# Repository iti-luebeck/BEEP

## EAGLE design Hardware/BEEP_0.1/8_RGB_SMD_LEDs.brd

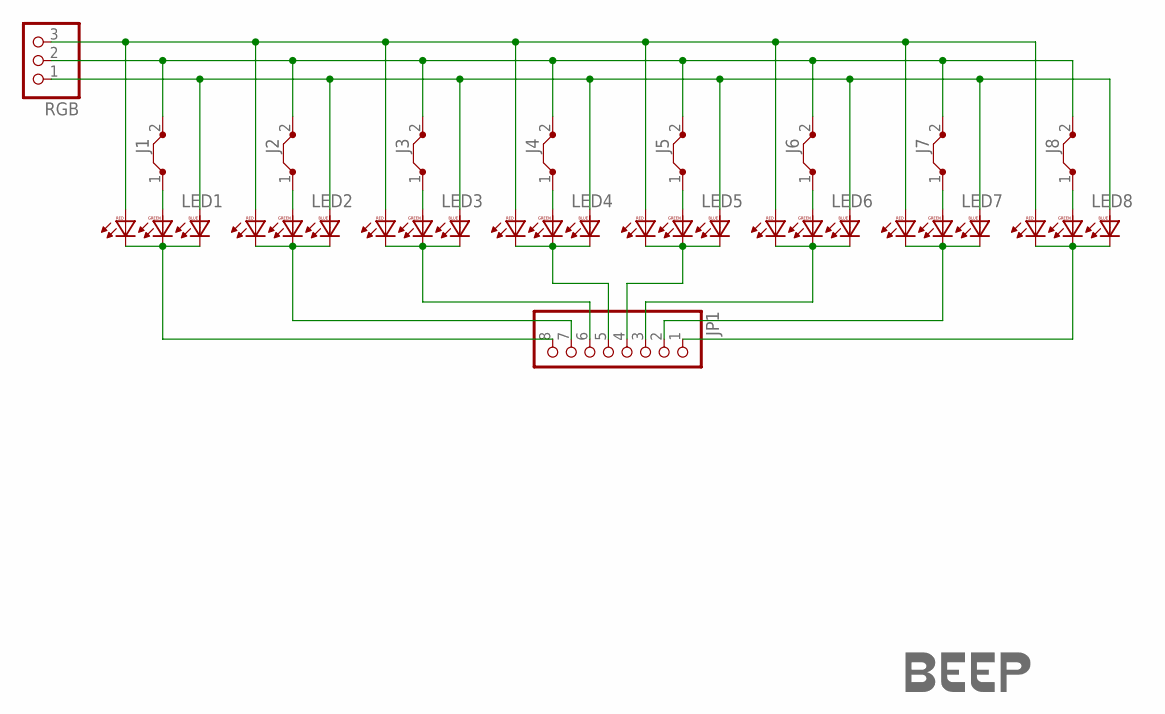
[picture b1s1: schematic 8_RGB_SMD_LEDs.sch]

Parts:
J1, J2, J3, J4, J5, J6, J7, J8: J7MM; 07
JP1: PINHD-1X8; 1X08
LED1, LED2, LED3, LED4, LED5, LED6, LED7, LED8: F503605050; 5050LED
RGB: PINHD-1X3; 1X03
U$5: LOGO-COPPER7; COPPER7

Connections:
unnamed: J1.2, J2.2, J3.2, J4.2, J5.2, J6.2, J7.2, J8.2, RGB.2
unnamed: J1.1, LED1.G1 (GA)
unnamed: JP1.8, LED1.B2 (BC), LED1.G2 (GC), LED1.R2 (RC)
unnamed: JP1.7, LED2.B2 (BC), LED2.G2 (GC), LED2.R2 (RC)
unnamed: JP1.6, LED3.B2 (BC), LED3.G2 (GC), LED3.R2 (RC)
unnamed: JP1.5, LED4.B2 (BC), LED4.G2 (GC), LED4.R2 (RC)
unnamed: J2.1, LED2.G1 (GA)
unnamed: JP1.4, LED5.B2 (BC), LED5.G2 (GC), LED5.R2 (RC)
unnamed: JP1.3, LED6.B2 (BC), LED6.G2 (GC), LED6.R2 (RC)
unnamed: JP1.2, LED7.B2 (BC), LED7.G2 (GC), LED7.R2 (RC)
unnamed: JP1.1, LED8.B2 (BC), LED8.G2 (GC), LED8.R2 (RC)
unnamed: J3.1, LED3.G1 (GA)
unnamed: J4.1, LED4.G1 (GA)
unnamed: J5.1, LED5.G1 (GA)
unnamed: J6.1, LED6.G1 (GA)
unnamed: J7.1, LED7.G1 (GA)
unnamed: LED1.R1 (RA), LED2.R1 (RA), LED3.R1 (RA), LED4.R1 (RA), LED5.R1 (RA), LED6.R1 (RA), LED7.R1 (RA), LED8.R1 (RA), RGB.3
unnamed: J8.1, LED8.G1 (GA)
unnamed: LED1.B1 (BA), LED2.B1 (BA), LED3.B1 (BA), LED4.B1 (BA), LED5.B1 (BA), LED6.B1 (BA), LED7.B1 (BA), LED8.B1 (BA), RGB.1

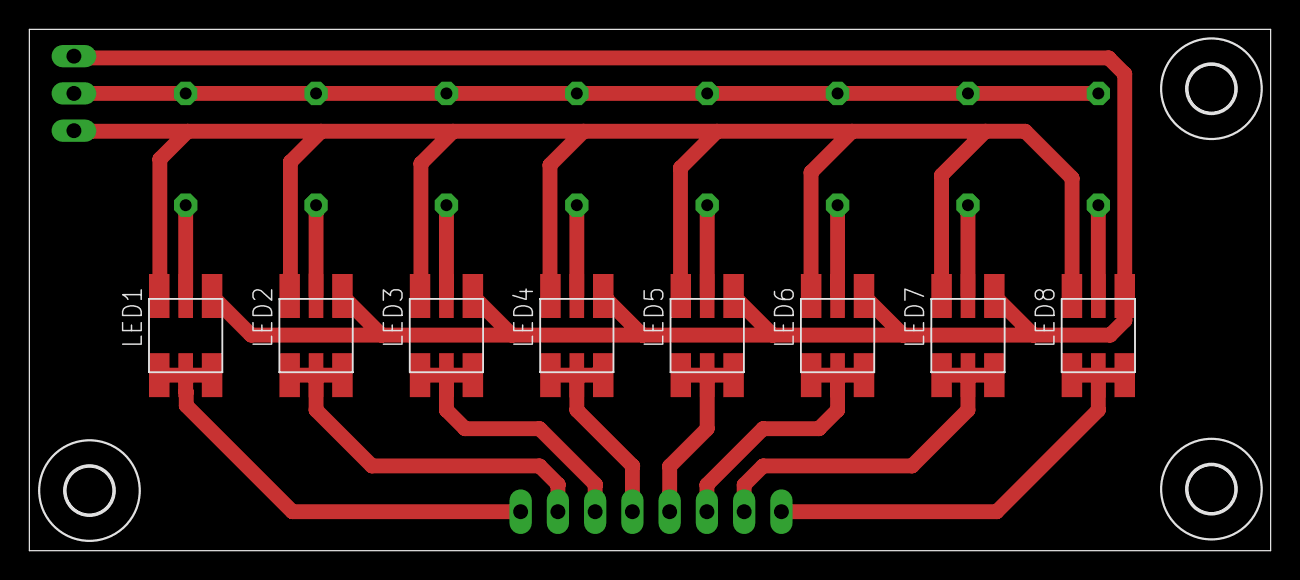
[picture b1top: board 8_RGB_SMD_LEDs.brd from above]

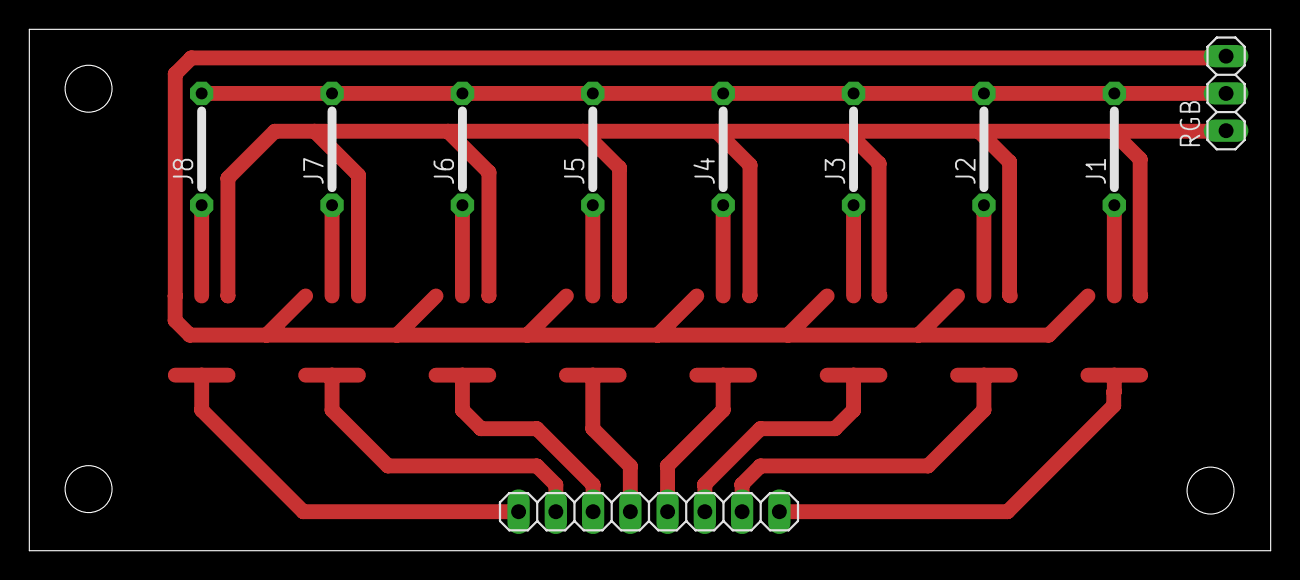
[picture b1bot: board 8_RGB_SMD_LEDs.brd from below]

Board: 2 copper layers, 84.6 x 35.5 mm, 22 parts (10 on the bottom side), 19 nets.

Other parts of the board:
U$1, U$2, U$3: 3,2

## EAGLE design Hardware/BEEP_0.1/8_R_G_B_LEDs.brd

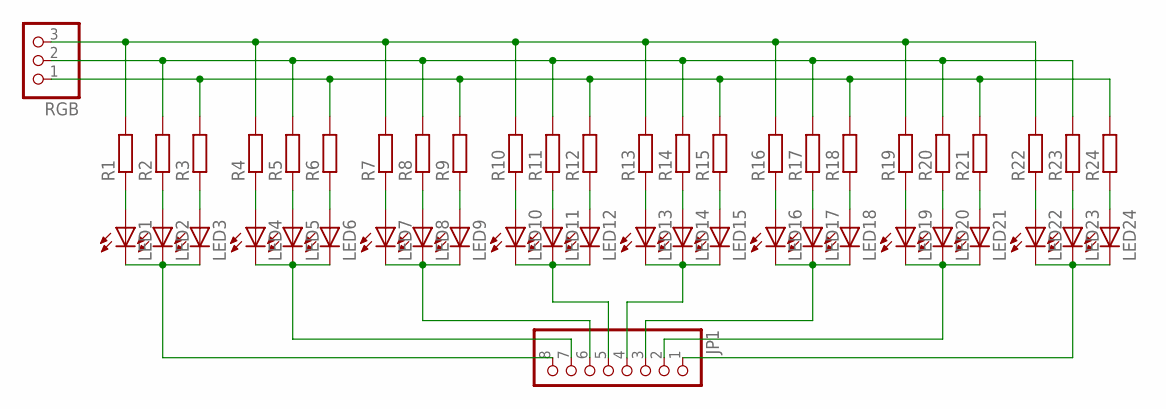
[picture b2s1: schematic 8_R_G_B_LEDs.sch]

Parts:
JP1: PINHD-1X8; 1X08
LED1, LED2, LED3, LED4, LED5, LED6, LED7, LED8, LED9, LED10, LED11, LED12, LED13, LED14, LED15, LED16, LED17, LED18, LED19, LED20, LED21, LED22, LED23, LED24: LED5MM
R1, R2, R3, R4, R5, R6, R7, R8, R9, R10, R11, R12, R13, R14, R15, R16, R17, R18, R19, R20, R21, R22, R23, R24: R-EU_0207/7; 0207/7
RGB: PINHD-1X3; 1X03

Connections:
unnamed: R1.2, R4.2, R7.2, R10.2, R13.2, R16.2, R19.2, R22.2, RGB.3
unnamed: R2.2, R5.2, R8.2, R11.2, R14.2, R17.2, R20.2, R23.2, RGB.2
unnamed: R3.2, R6.2, R9.2, R12.2, R15.2, R18.2, R21.2, R24.2, RGB.1
unnamed: LED1.A, R1.1
unnamed: LED2.A, R2.1
unnamed: LED3.A, R3.1
unnamed: JP1.8, LED1.K (C), LED2.K (C), LED3.K (C)
unnamed: JP1.7, LED4.K (C), LED5.K (C), LED6.K (C)
unnamed: JP1.6, LED7.K (C), LED8.K (C), LED9.K (C)
unnamed: JP1.5, LED10.K (C), LED11.K (C), LED12.K (C)
unnamed: LED4.A, R4.1
unnamed: LED5.A, R5.1
unnamed: LED6.A, R6.1
unnamed: JP1.4, LED13.K (C), LED14.K (C), LED15.K (C)
unnamed: JP1.3, LED16.K (C), LED17.K (C), LED18.K (C)
unnamed: JP1.2, LED19.K (C), LED20.K (C), LED21.K (C)
unnamed: JP1.1, LED22.K (C), LED23.K (C), LED24.K (C)
unnamed: LED7.A, R7.1
unnamed: LED8.A, R8.1
unnamed: LED9.A, R9.1
unnamed: LED10.A, R10.1
unnamed: LED11.A, R11.1
unnamed: LED12.A, R12.1
unnamed: LED13.A, R13.1
unnamed: LED14.A, R14.1
unnamed: LED15.A, R15.1
unnamed: LED16.A, R16.1
unnamed: LED17.A, R17.1
unnamed: LED18.A, R18.1
unnamed: LED19.A, R19.1
unnamed: LED20.A, R20.1
unnamed: LED21.A, R21.1
unnamed: LED22.A, R22.1
unnamed: LED23.A, R23.1
unnamed: LED24.A, R24.1

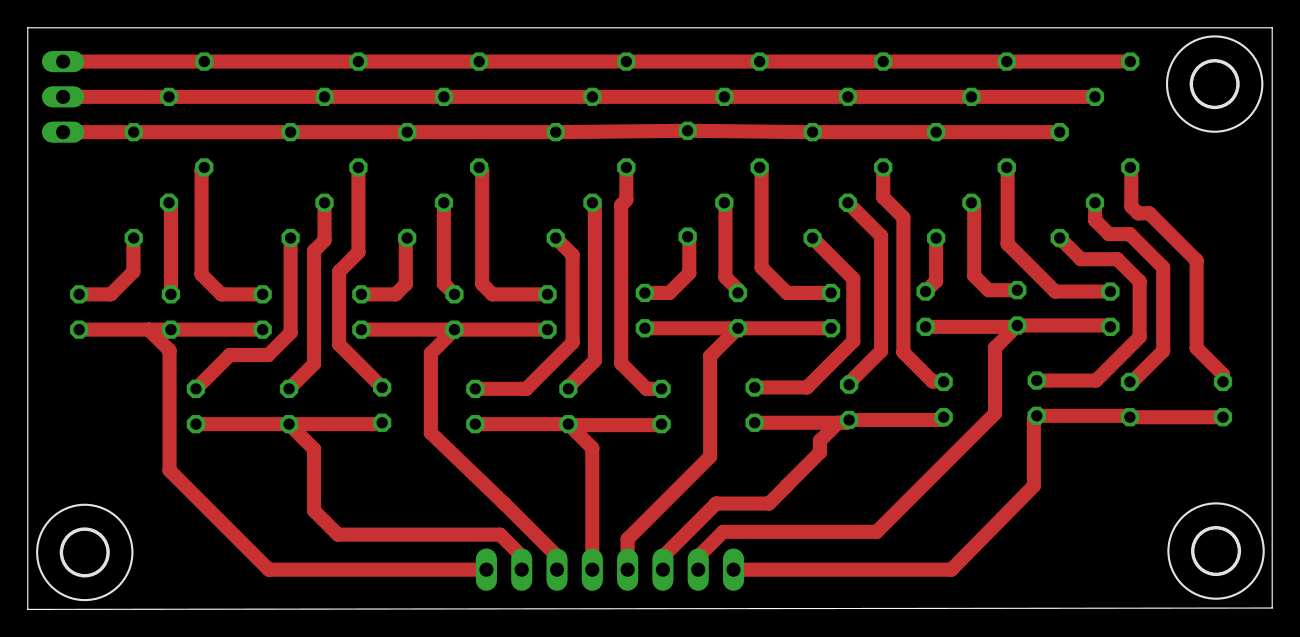
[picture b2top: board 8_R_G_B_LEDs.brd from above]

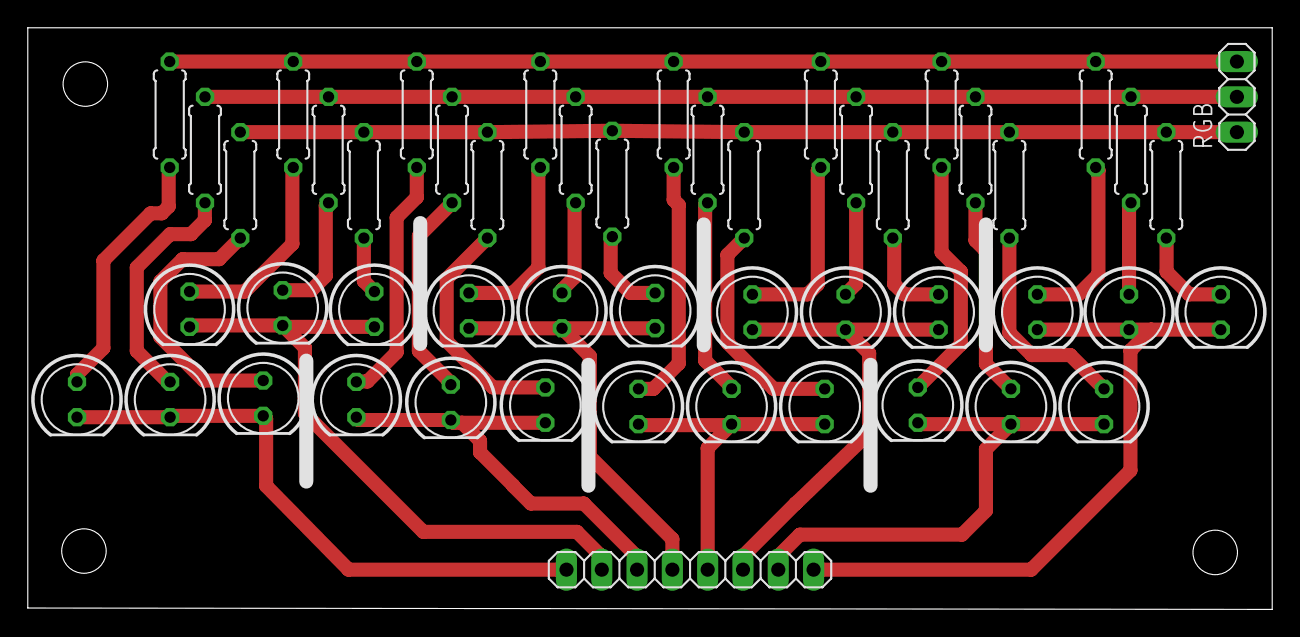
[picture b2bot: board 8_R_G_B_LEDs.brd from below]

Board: 2 copper layers, 89.5 x 41.9 mm, 53 parts (50 on the bottom side), 35 nets.

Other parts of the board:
U$1, U$2, U$3: 3,2

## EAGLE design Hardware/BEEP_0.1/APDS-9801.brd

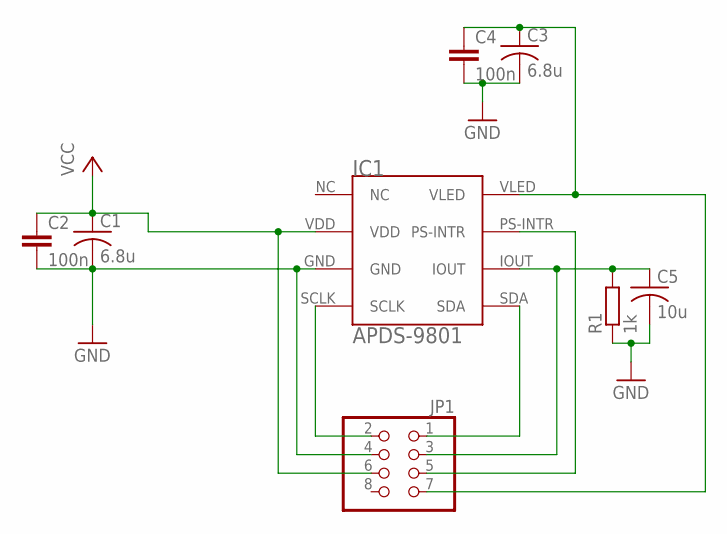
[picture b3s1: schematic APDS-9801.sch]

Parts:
C1, C3: 6.8u; C025-024X044
C2, C4: 100n; C0805
C5: 10u; C025-024X044
IC1: APDS-9801
JP1: PINHD-2X4; 2X04
R1: 1k; M0805

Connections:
GND: C1.2, C2.2, C3.2, C4.2, C5.2, IC1.GND, JP1.4, R1.1
unnamed: IC1.PS-INTR, JP1.5
unnamed: C5.1, IC1.IOUT, JP1.3, R1.2
unnamed: C3.1, C4.1, IC1.VLED, JP1.7
unnamed: IC1.SCLK, JP1.2
unnamed: IC1.SDA, JP1.1
VCC: C1.1, C2.1, IC1.VDD, JP1.6

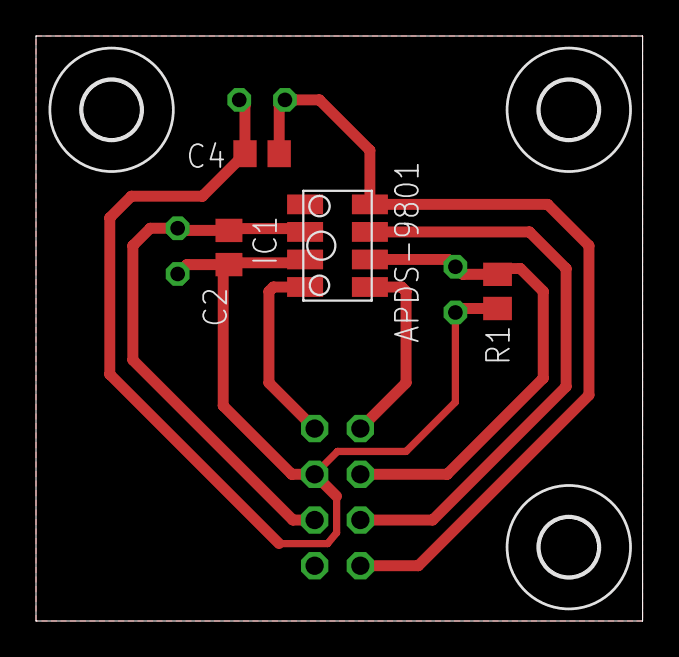
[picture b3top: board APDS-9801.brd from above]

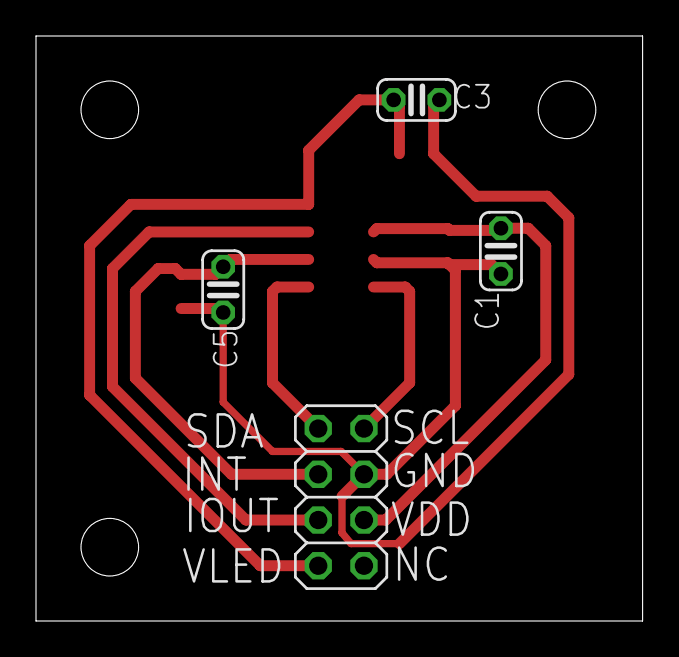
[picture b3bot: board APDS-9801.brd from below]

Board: 2 copper layers, 33.7 x 32.5 mm, 12 parts (4 on the bottom side), 7 nets.

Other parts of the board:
U$1: COPPER4
U$3, U$4, U$5: 3,2

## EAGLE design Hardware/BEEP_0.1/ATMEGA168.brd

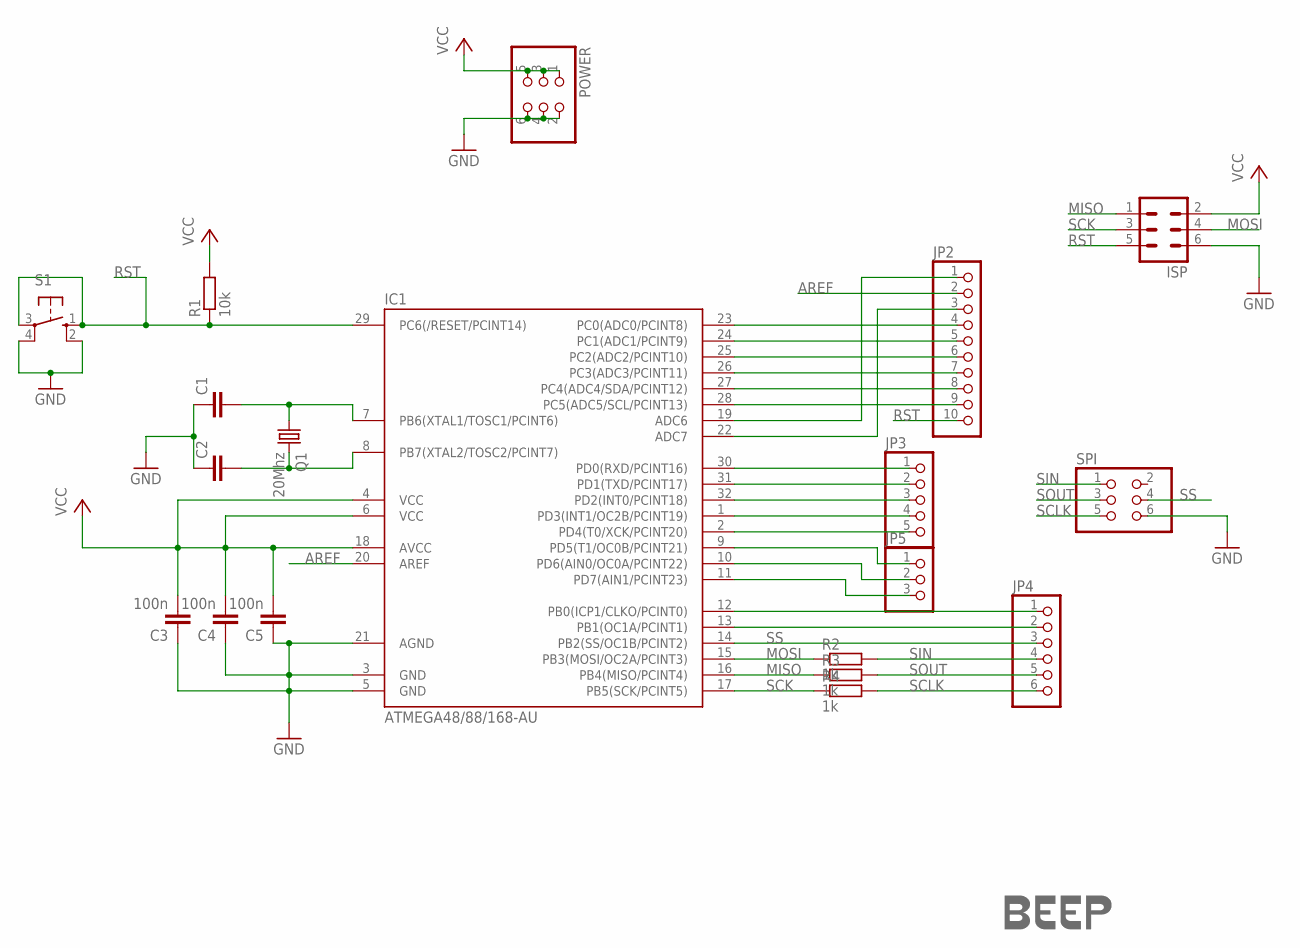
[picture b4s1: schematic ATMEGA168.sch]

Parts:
C1, C2: C-EUC0805; C0805
C3, C4: 100n; C0805
C5: 100n; C050-025X075
IC1: ATMEGA48/88/168-AU; TQFP32-08
ISP: ML6
JP2: PINHD-1X10; 1X10
JP3: PINHD-1X5; 1X05
JP4: PINHD-1X6; 1X06
JP5: PINHD-1X3; 1X03
POWER: PINHD-2X3; 2X03
Q1: 20Mhz; HC49/S
R1: 10k; M0805
R2, R3, R4: 1k; 0207/7
S1: 10-XX; B3F-10XX
SPI: PINHD-2X3; 2X03
U$1: LOGO-COPPER4; COPPER4

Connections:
AREF: IC1.20 (AREF), JP2.2
GND: C1.1, C2.1, C3.1, C4.1, C5.1, IC1.3 (GND), IC1.5 (GND), IC1.21 (AGND), ISP.6, POWER.2, POWER.4, POWER.6, S1.2 (S1), S1.4 (P1), SPI.6
MISO: IC1.16 (PB4(MISO/PCINT4)), ISP.1, R3.1
MOSI: IC1.15 (PB3(MOSI/OC2A/PCINT3)), ISP.4, R2.1
unnamed: C1.2, IC1.7 (PB6(XTAL1/TOSC1/PCINT6)), Q1.1
unnamed: C2.2, IC1.8 (PB7(XTAL2/TOSC2/PCINT7)), Q1.2
unnamed: IC1.28 (PC5(ADC5/SCL/PCINT13)), JP2.9
unnamed: IC1.27 (PC4(ADC4/SDA/PCINT12)), JP2.8
unnamed: IC1.26 (PC3(ADC3/PCINT11)), JP2.7
unnamed: IC1.25 (PC2(ADC2/PCINT10)), JP2.6
unnamed: IC1.9 (PD5(T1/OC0B/PCINT21)), JP5.1
unnamed: IC1.10 (PD6(AIN0/OC0A/PCINT22)), JP5.2
unnamed: IC1.30 (PD0(RXD/PCINT16)), JP3.1
unnamed: IC1.31 (PD1(TXD/PCINT17)), JP3.2
unnamed: IC1.32 (PD2(INT0/PCINT18)), JP3.3
unnamed: IC1.1 (PD3(INT1/OC2B/PCINT19)), JP3.4
unnamed: IC1.2 (PD4(T0/XCK/PCINT20)), JP3.5
unnamed: IC1.11 (PD7(AIN1/PCINT23)), JP5.3
unnamed: IC1.24 (PC1(ADC1/PCINT9)), JP2.5
unnamed: IC1.23 (PC0(ADC0/PCINT8)), JP2.4
unnamed: IC1.12 (PB0(ICP1/CLKO/PCINT0)), JP4.1
unnamed: IC1.13 (PB1(OC1A/PCINT1)), JP4.2
unnamed: IC1.19 (ADC6), JP2.1
unnamed: IC1.22 (ADC7), JP2.3
RST: IC1.29 (PC6(/RESET/PCINT14)), ISP.5, JP2.10, R1.1, S1.1 (S), S1.3
SCK: IC1.17 (PB5(SCK/PCINT5)), ISP.3, R4.1
SCLK: JP4.6, R4.2, SPI.5
SIN: JP4.4, R2.2, SPI.1
SOUT: JP4.5, R3.2, SPI.3
SS: IC1.14 (PB2(SS/OC1B/PCINT2)), JP4.3, SPI.4
VCC: C3.2, C4.2, C5.2, IC1.4 (VCC), IC1.6 (VCC), IC1.18 (AVCC), ISP.2, POWER.1, POWER.3, POWER.5, R1.2

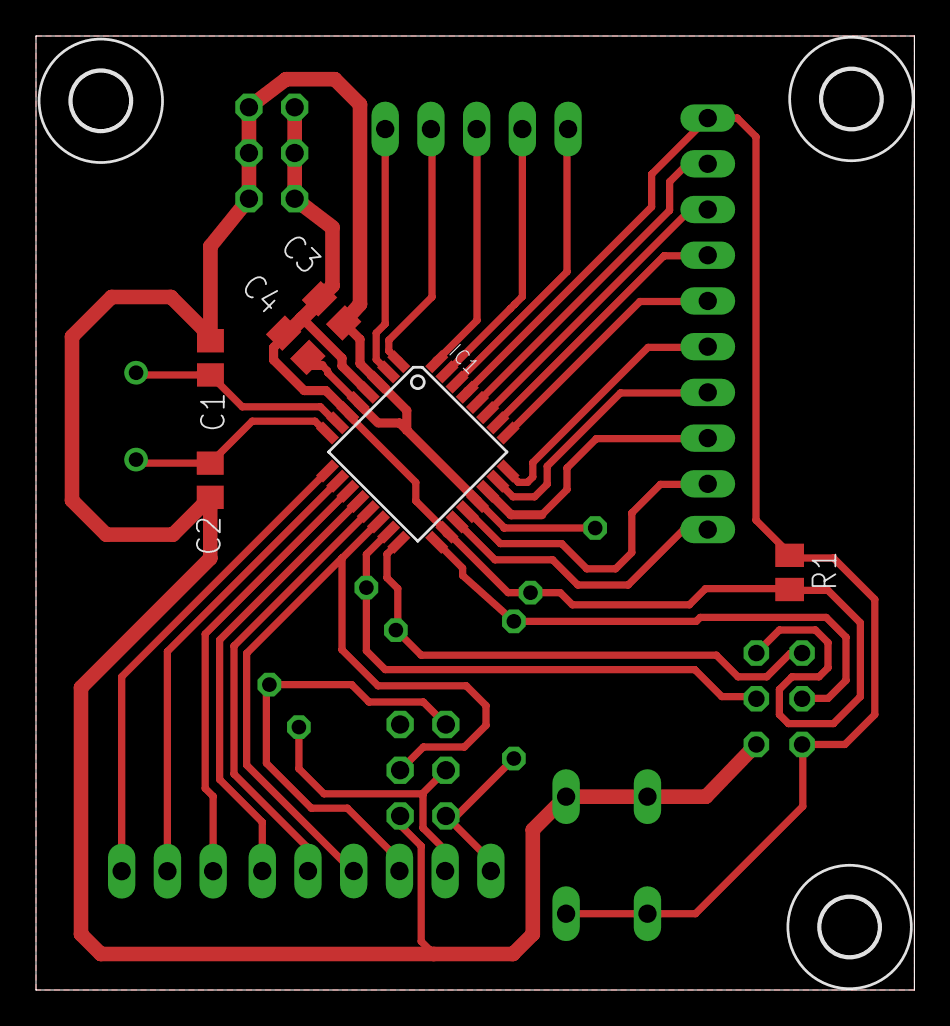
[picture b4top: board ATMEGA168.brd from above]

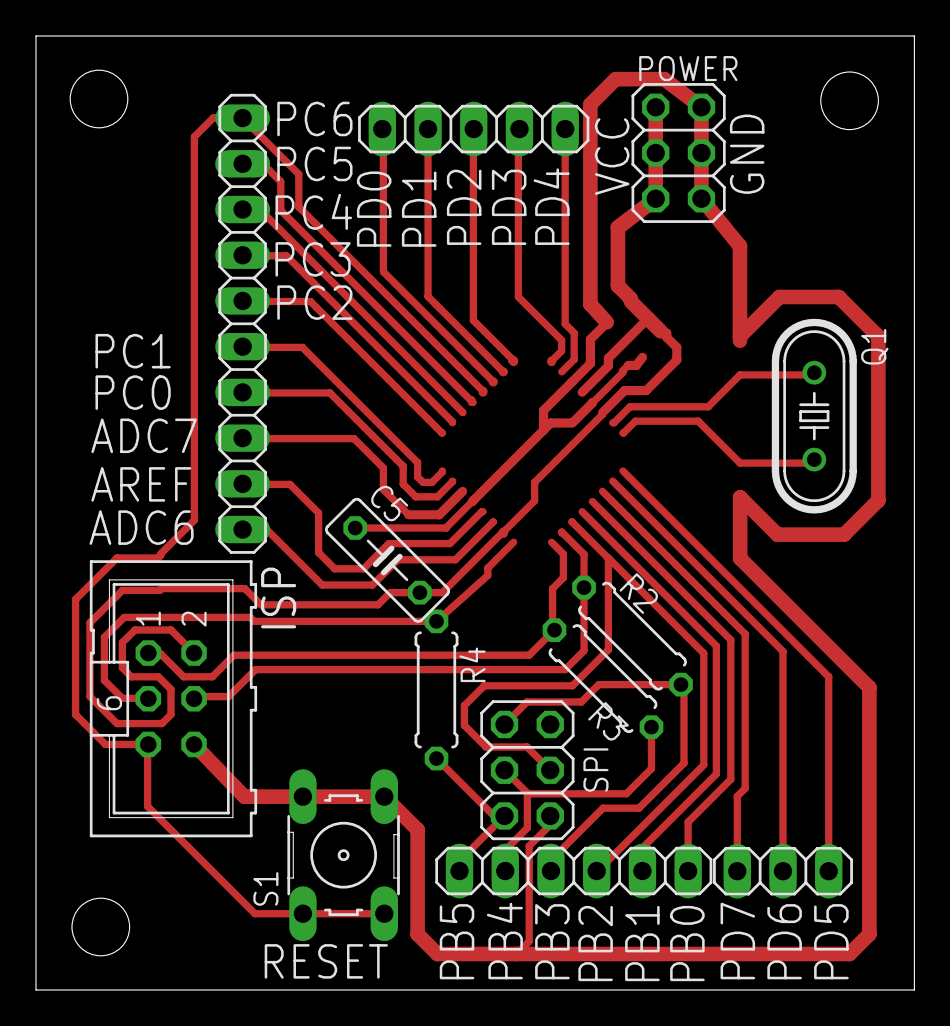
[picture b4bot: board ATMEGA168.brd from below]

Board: 2 copper layers, 48.8 x 53.0 mm, 23 parts (13 on the bottom side), 31 nets.

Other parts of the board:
H1, H2, H3: 3,2

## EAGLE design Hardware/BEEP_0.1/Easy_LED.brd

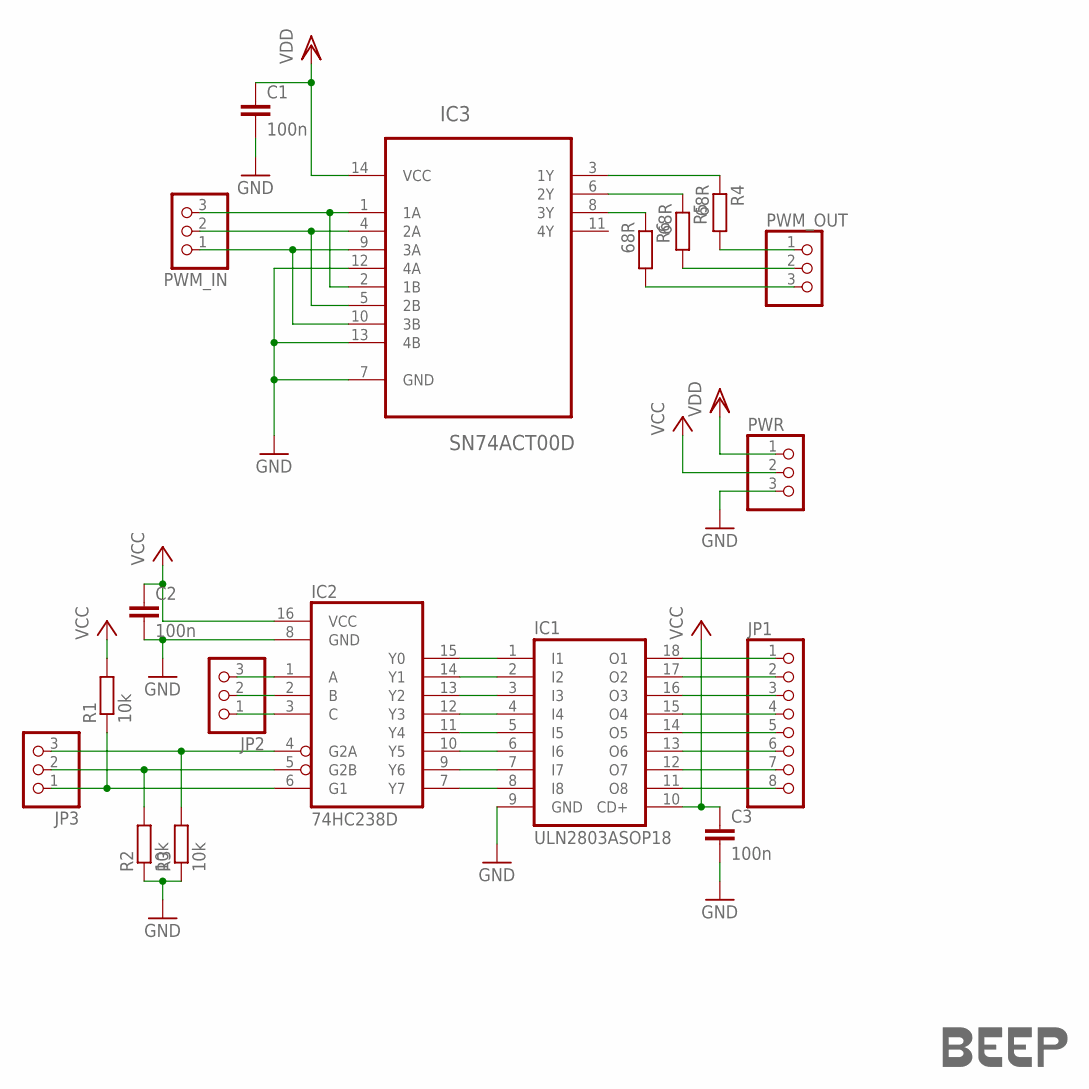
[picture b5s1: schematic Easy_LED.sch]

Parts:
C1, C2, C3: 100n; C0805
IC1: ULN2803ASOP18; SOP18
IC2: 74HC238D; SO16
IC3: SN74ACT00D; SOIC127P600X175-14N
JP1: PINHD-1X8; 1X08
JP2, JP3: PINHD-1X3; 1X03
PWM_IN: PINHD-1X3; 1X03
PWM_OUT: PINHD-1X3; 1X03
PWR: PINHD-1X3; 1X03
R1: 10k; 0207/7
R2, R3: 10k; M0805
R4, R5, R6: 68R; M0805
U$4: LOGO-COPPER6; COPPER6

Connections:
GND: C1.2, C2.2, C3.2, IC1.9 (GND), IC2.8 (GND), IC3.7 (GND), IC3.12 (4A), IC3.13 (4B), PWR.3, R2.1, R3.1
unnamed: IC1.17 (O2), JP1.2
unnamed: IC1.16 (O3), JP1.3
unnamed: IC1.15 (O4), JP1.4
unnamed: IC1.14 (O5), JP1.5
unnamed: IC1.13 (O6), JP1.6
unnamed: IC1.12 (O7), JP1.7
unnamed: IC1.18 (O1), JP1.1
unnamed: IC1.1 (I1), IC2.15 (Y0)
unnamed: IC1.2 (I2), IC2.14 (Y1)
unnamed: IC1.3 (I3), IC2.13 (Y2)
unnamed: IC1.11 (O8), JP1.8
unnamed: IC3.1 (1A), IC3.2 (1B), PWM_IN.3
unnamed: IC3.4 (2A), IC3.5 (2B), PWM_IN.2
unnamed: IC3.9 (3A), IC3.10 (3B), PWM_IN.1
unnamed: IC1.4 (I4), IC2.12 (Y3)
unnamed: IC1.5 (I5), IC2.11 (Y4)
unnamed: IC1.6 (I6), IC2.10 (Y5)
unnamed: PWM_OUT.3, R6.2
unnamed: PWM_OUT.2, R5.2
unnamed: PWM_OUT.1, R4.2
unnamed: IC3.3 (1Y), R4.1
unnamed: IC1.7 (I7), IC2.9 (Y6)
unnamed: IC1.8 (I8), IC2.7 (Y7)
unnamed: IC2.1 (A), JP2.3
unnamed: IC3.6 (2Y), R5.1
unnamed: IC3.8 (3Y), R6.1
unnamed: IC2.2 (B), JP2.2
unnamed: IC2.3 (C), JP2.1
unnamed: IC2.4 (G2A), JP3.3, R3.2
unnamed: IC2.5 (G2B), JP3.2, R2.2
unnamed: IC2.6 (G1), JP3.1, R1.1
VCC: C2.1, C3.1, IC1.10 (CD+), IC2.16 (VCC), PWR.2, R1.2
VDD: C1.1, IC3.14 (VCC), PWR.1

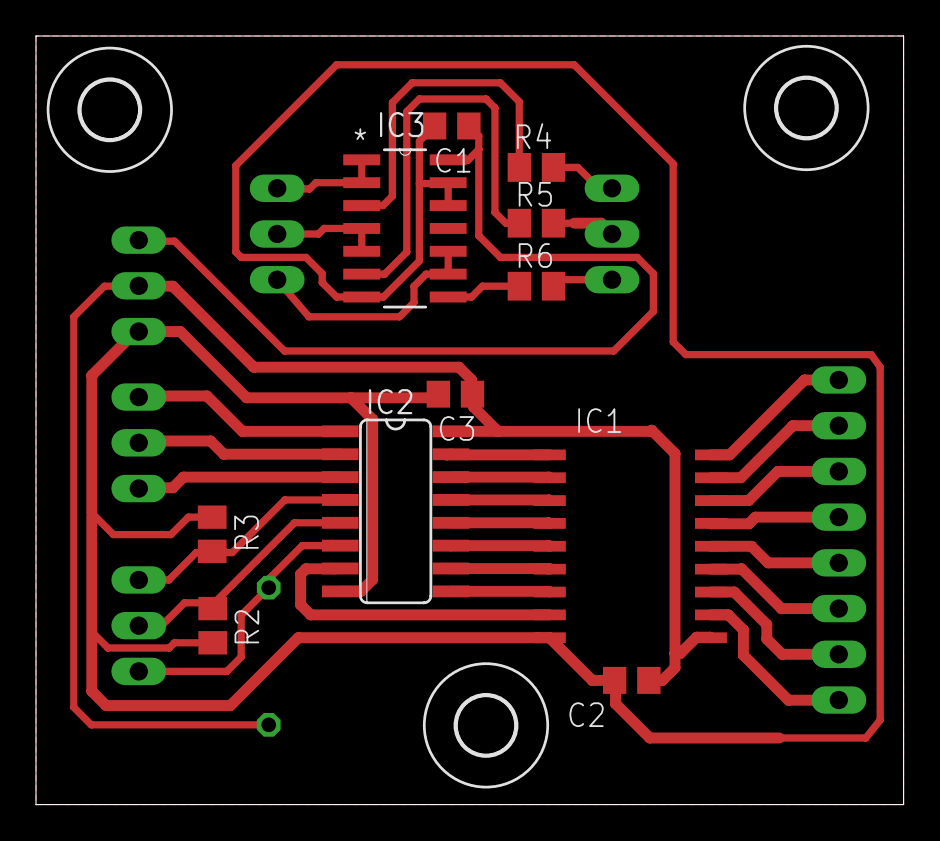
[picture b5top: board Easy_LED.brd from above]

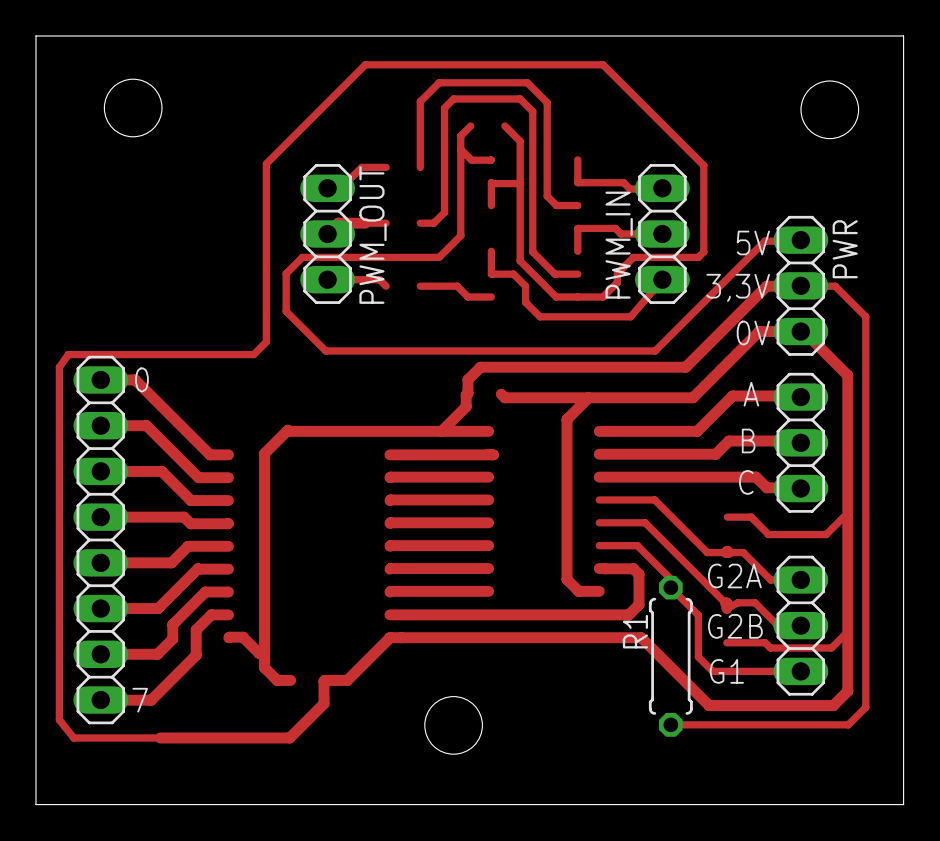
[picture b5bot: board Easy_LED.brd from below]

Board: 2 copper layers, 48.2 x 42.7 mm, 22 parts (7 on the bottom side), 34 nets.

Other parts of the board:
U$1, U$2, U$3: 3,2

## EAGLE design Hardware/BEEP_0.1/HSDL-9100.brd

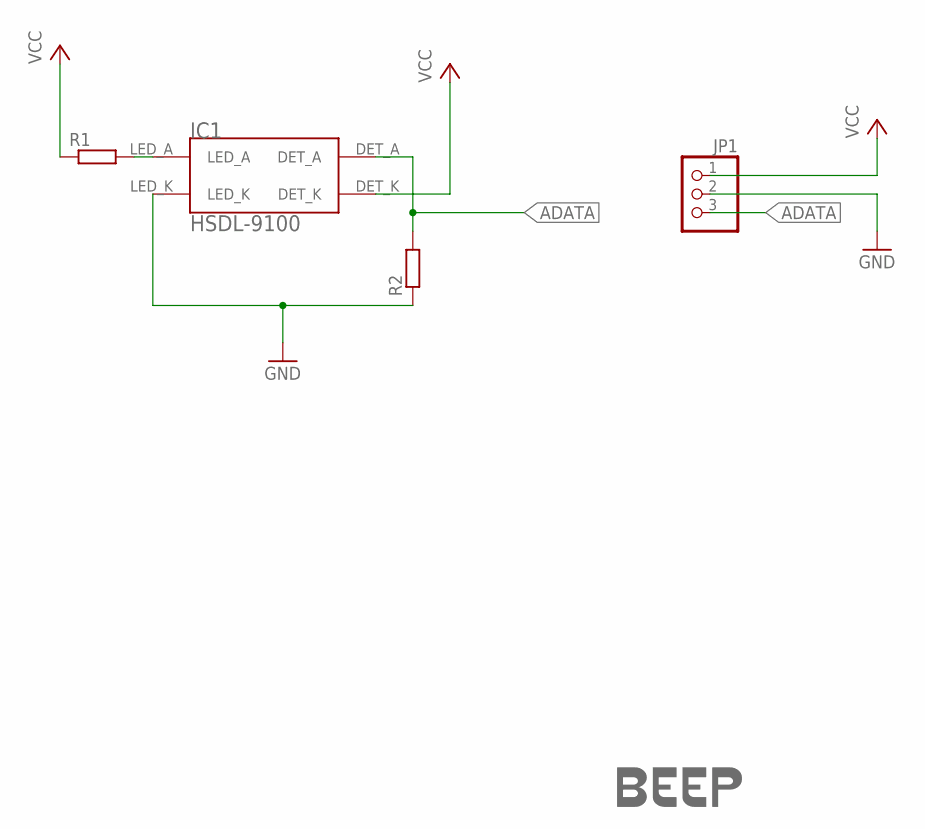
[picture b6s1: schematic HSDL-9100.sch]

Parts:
IC1: HSDL-9100
JP1: PINHD-1X3; 1X03
R1, R2: R-EU_M0805; M0805
U$1: LOGO-COPPER3; COPPER3

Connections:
ADATA: IC1.DET_A, JP1.3, R2.2
GND: IC1.LED_K, JP1.2, R2.1
unnamed: IC1.LED_A, R1.2
VCC: IC1.DET_K, JP1.1, R1.1

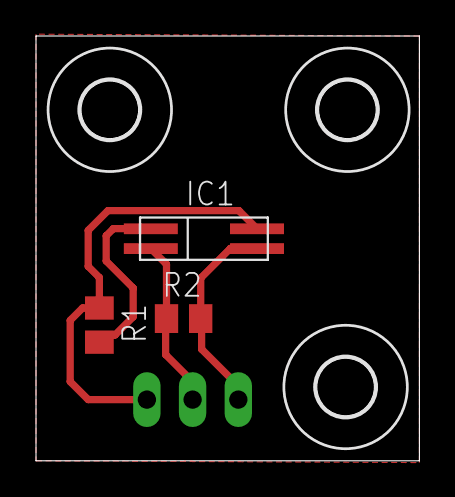
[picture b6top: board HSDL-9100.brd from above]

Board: 2 copper layers, 21.3 x 23.6 mm, 8 parts (1 on the bottom side), 4 nets.

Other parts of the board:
U$2, U$3, U$4: 3,2

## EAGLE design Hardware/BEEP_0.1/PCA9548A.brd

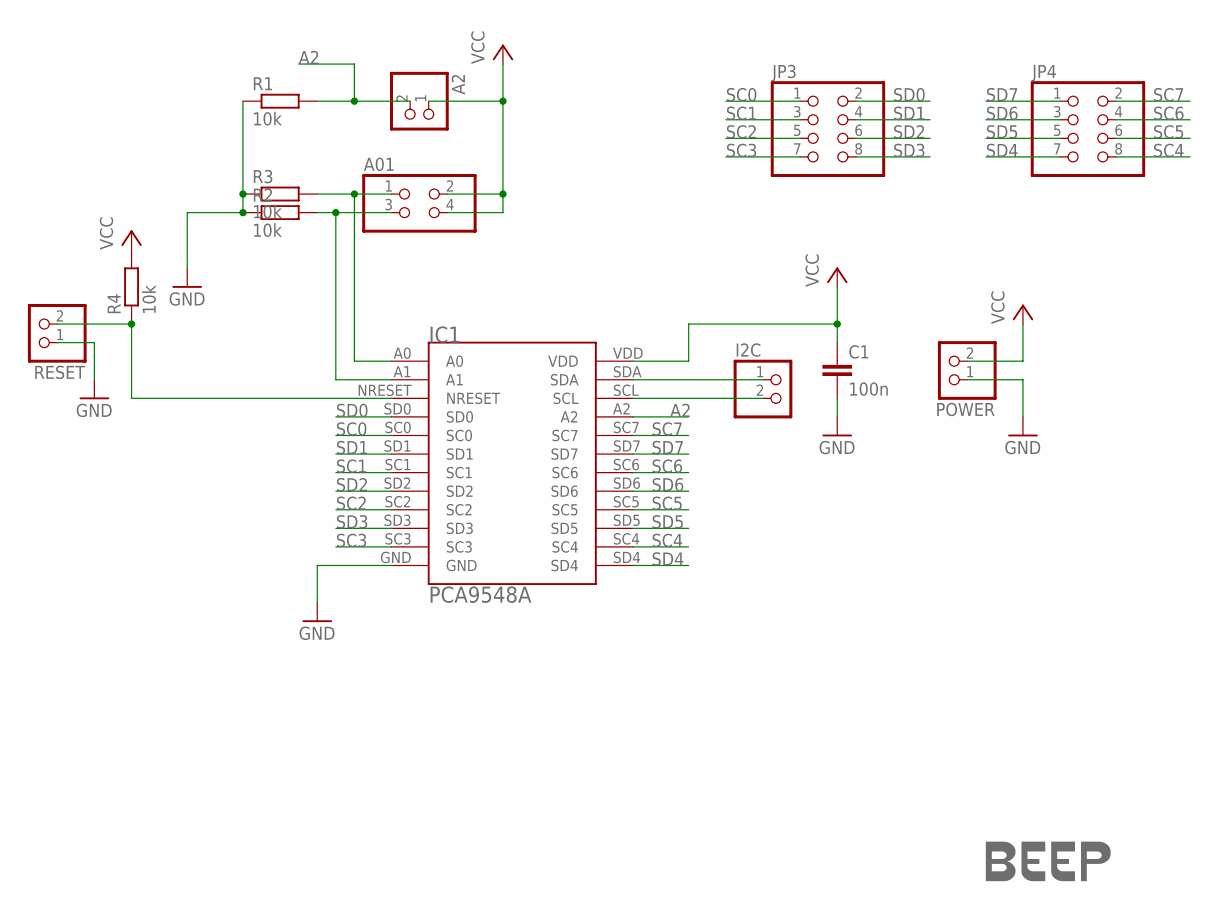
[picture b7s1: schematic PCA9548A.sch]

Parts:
A01: PINHD-2X2; 2X02
A2: PINHD-1X2; 1X02
C1: 100n; C0805
I2C: PINHD-1X2; 1X02
IC1: PCA9548A; TSSOP24
JP3, JP4: PINHD-2X4; 2X04
POWER: PINHD-1X2; 1X02
R1, R2, R3: 10k; 0207/7
R4: 10k; M0805
RESET: PINHD-1X2; 1X02
U$1: LOGO-COPPER4; COPPER4

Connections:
A2: A2.2, IC1.A2, R1.2
GND: C1.2, IC1.GND, POWER.1, R1.1, R2.1, R3.1, RESET.1
I"C: I2C.1, IC1.SDA
unnamed: IC1.NRESET, R4.1, RESET.2
unnamed: A01.1, IC1.A0, R3.2
unnamed: I2C.2, IC1.SCL
unnamed: A01.3, IC1.A1, R2.2
SC0: IC1.SC0, JP3.1
SC1: IC1.SC1, JP3.3
SC2: IC1.SC2, JP3.5
SC3: IC1.SC3, JP3.7
SC4: IC1.SC4, JP4.8
SC5: IC1.SC5, JP4.6
SC6: IC1.SC6, JP4.4
SC7: IC1.SC7, JP4.2
SD0: IC1.SD0, JP3.2
SD1: IC1.SD1, JP3.4
SD2: IC1.SD2, JP3.6
SD3: IC1.SD3, JP3.8
SD4: IC1.SD4, JP4.7
SD5: IC1.SD5, JP4.5
SD6: IC1.SD6, JP4.3
SD7: IC1.SD7, JP4.1
VCC: A01.2, A01.4, A2.1, C1.1, IC1.VDD, POWER.2, R4.2

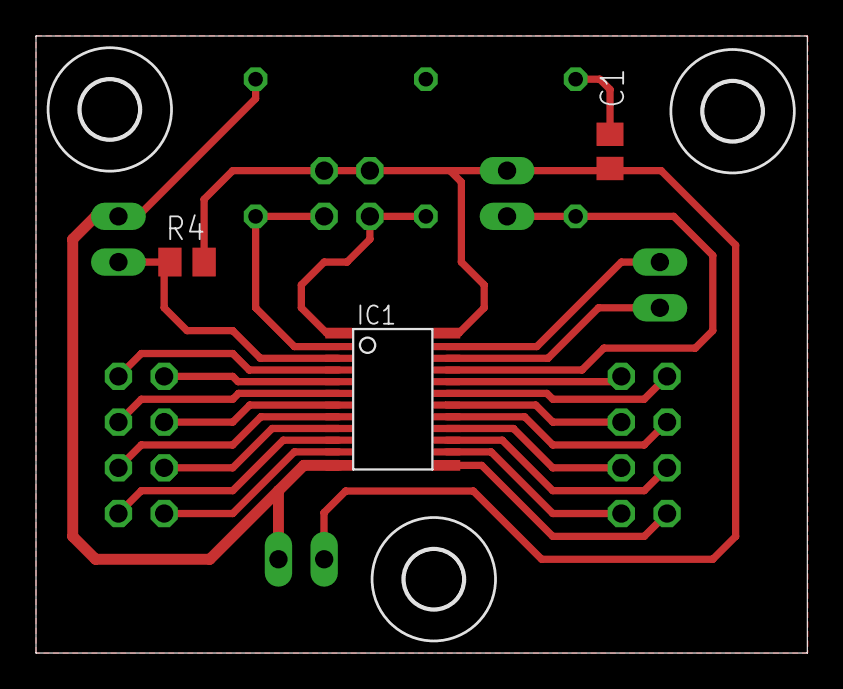
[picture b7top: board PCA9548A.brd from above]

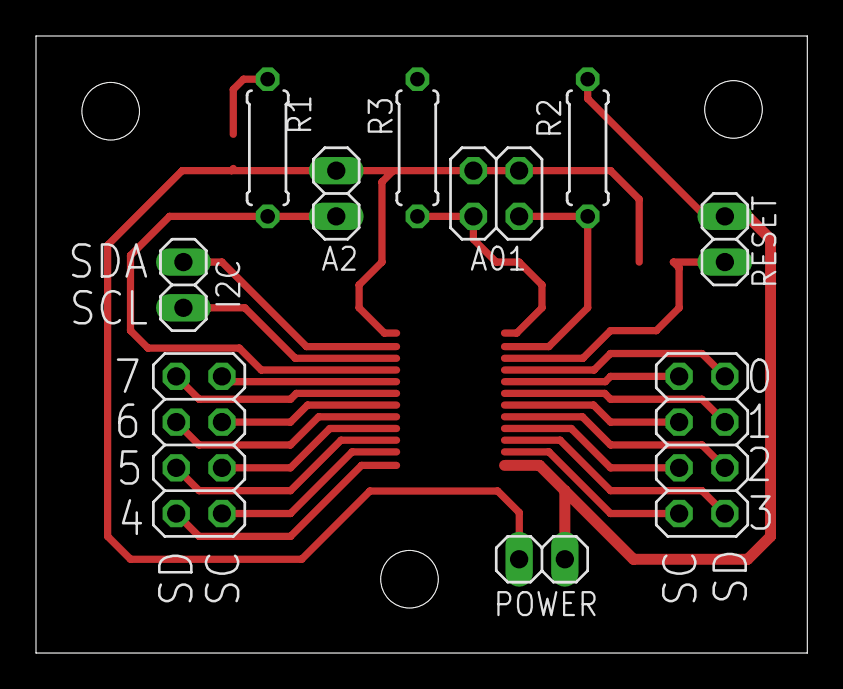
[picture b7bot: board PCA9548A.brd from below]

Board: 2 copper layers, 42.9 x 34.3 mm, 17 parts (10 on the bottom side), 24 nets.

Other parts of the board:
U$2, U$3, U$4: 3,2
